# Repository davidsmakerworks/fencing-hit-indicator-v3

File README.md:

# fencing-hit-indicator-v3
 Fencing hit indicator with score display

## Possible future enhancements:
* Add score increment pads on PCB
* Redesign PCB for more efficient space usage
* Design separate LED PCBs with ribbon cable from main PCB
* Add bout clock
* Add compile-time option to select PWM buzzer or active buzzer
* Reduce LED current (increase value of R2 and R3)

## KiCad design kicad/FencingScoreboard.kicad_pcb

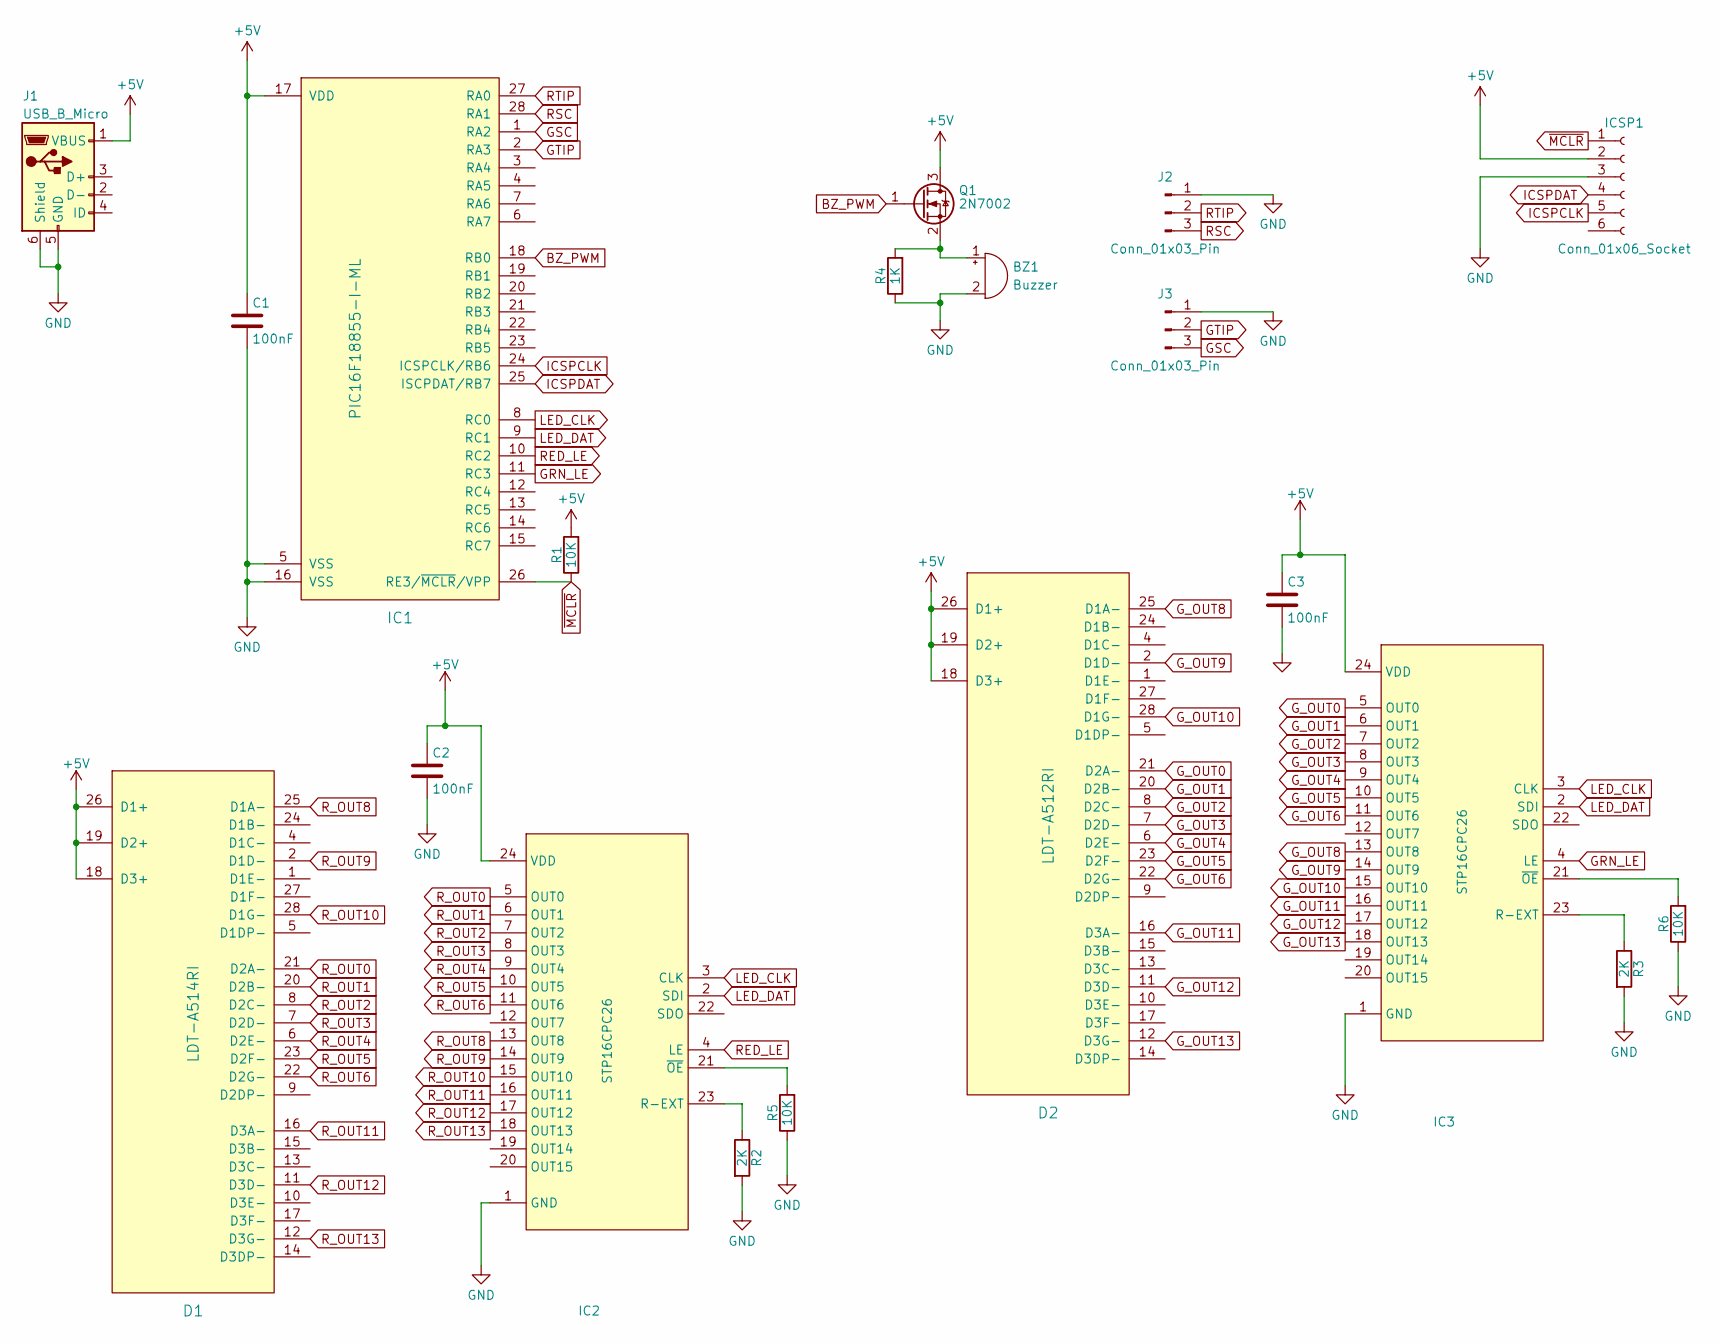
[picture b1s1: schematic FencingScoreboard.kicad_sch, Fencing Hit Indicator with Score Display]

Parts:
BZ1: Buzzer; MagneticBuzzer_ProSignal_ABT-410-RC
C1, C2, C3: 100nF; C_0603_1608Metric
D1: LDT-A514RI; LDT-x51xRI
D2: LDT-A512RI; LDT-x51xRI
IC1: PIC16F18855-I-ML; QFN-28-1EP_6x6mm_P0.65mm_EP4.25x4.25mm
IC2, IC3: STP16CPC26; SOP-24_7.5x15.4mm_P1.27mm
ICSP1: Conn_01x06_Socket; PinHeader_1x06_P2.54mm_Vertical
J1: USB_B_Micro; Molex_105164-0001_MicroUSB
J2, J3: Conn_01x03_Pin; PinHeader_1x03_P2.54mm_Vertical
Q1: 2N7002; SOT-23
R1, R5, R6: 10K; R_0805_2012Metric
R2, R3: 2K; R_0805_2012Metric
R4: 1K; R_0805_2012Metric

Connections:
+5V: C1.1, C2.1, C3.1, D1.18 (D3+), D1.19 (D2+), D1.26 (D1+), D2.18 (D3+), D2.19 (D2+), D2.26 (D1+), IC1.17 (VDD), IC2.24 (VDD), IC3.24 (VDD), ICSP1.2, J1.1 (VBUS), Q1.3 (D), R1.2
BZ_PWM: IC1.18 (RB0), Q1.1 (G)
GND: BZ1.2 (+), C1.2, C2.2, C3.2, IC1.5 (VSS), IC1.16 (VSS), IC2.1 (GND), IC3.1 (GND), ICSP1.3, J1.5 (GND), J1.6 (Shield), J2.1, J3.1, R2.2, R3.2, R4.1, R5.1, R6.1
GRN_LE: IC1.11 (RC3), IC3.4 (LE)
GSC: IC1.1 (RA2), J3.3
GTIP: IC1.2 (RA3), J3.2
G_OUT0: D2.21 (D2A-), IC3.5 (OUT0)
G_OUT1: D2.20 (D2B-), IC3.6 (OUT1)
G_OUT2: D2.8 (D2C-), IC3.7 (OUT2)
G_OUT3: D2.7 (D2D-), IC3.8 (OUT3)
G_OUT4: D2.6 (D2E-), IC3.9 (OUT4)
G_OUT5: D2.23 (D2F-), IC3.10 (OUT5)
G_OUT6: D2.22 (D2G-), IC3.11 (OUT6)
G_OUT8: D2.25 (D1A-), IC3.13 (OUT8)
G_OUT9: D2.2 (D1D-), IC3.14 (OUT9)
G_OUT10: D2.28 (D1G-), IC3.15 (OUT10)
G_OUT11: D2.16 (D3A-), IC3.16 (OUT11)
G_OUT12: D2.11 (D3D-), IC3.17 (OUT12)
G_OUT13: D2.12 (D3G-), IC3.18 (OUT13)
ICSPCLK: IC1.24 (ICSPCLK/RB6), ICSP1.5
ICSPDAT: IC1.25 (ISCPDAT/RB7), ICSP1.4
LED_CLK: IC1.8 (RC0), IC2.3 (CLK), IC3.3 (CLK)
LED_DAT: IC1.9 (RC1), IC2.2 (SDI), IC3.2 (SDI)
unnamed: BZ1.1 (-), Q1.2 (S), R4.2
unnamed: IC2.23 (R-EXT), R2.1
unnamed: IC2.21 (~OE), R5.2
unnamed: IC3.23 (R-EXT), R3.1
unnamed: IC3.21 (~OE), R6.2
RED_LE: IC1.10 (RC2), IC2.4 (LE)
RSC: IC1.28 (RA1), J2.3
RTIP: IC1.27 (RA0), J2.2
R_OUT0: D1.21 (D2A-), IC2.5 (OUT0)
R_OUT1: D1.20 (D2B-), IC2.6 (OUT1)
R_OUT2: D1.8 (D2C-), IC2.7 (OUT2)
R_OUT3: D1.7 (D2D-), IC2.8 (OUT3)
R_OUT4: D1.6 (D2E-), IC2.9 (OUT4)
R_OUT5: D1.23 (D2F-), IC2.10 (OUT5)
R_OUT6: D1.22 (D2G-), IC2.11 (OUT6)
R_OUT8: D1.25 (D1A-), IC2.13 (OUT8)
R_OUT9: D1.2 (D1D-), IC2.14 (OUT9)
R_OUT10: D1.28 (D1G-), IC2.15 (OUT10)
R_OUT11: D1.16 (D3A-), IC2.16 (OUT11)
R_OUT12: D1.11 (D3D-), IC2.17 (OUT12)
R_OUT13: D1.12 (D3G-), IC2.18 (OUT13)
~MCLR: IC1.26 (RE3/~MCLR/VPP), ICSP1.1, R1.1

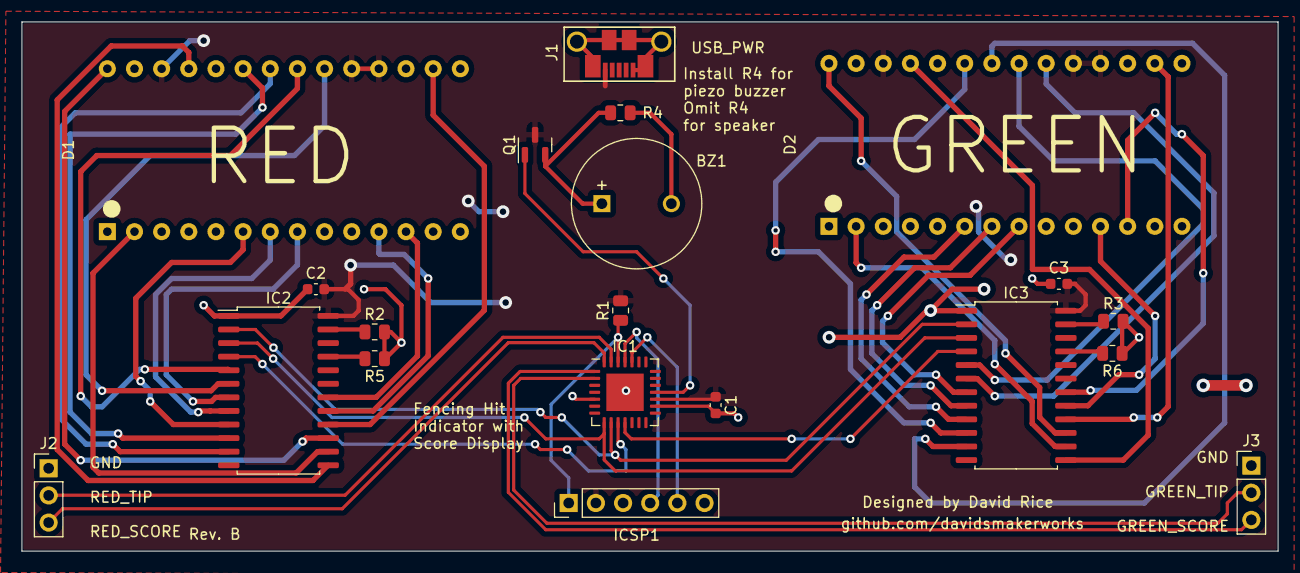
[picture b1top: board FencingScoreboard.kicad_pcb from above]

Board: 2 copper layers, 117.5 x 49.5 mm, 20 parts (0 on the bottom side), 45 nets.

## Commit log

2023-06-28 Minimal working version
2023-07-01 Add score limit and auto-reset
2023-07-01 Comments and minor cleanup
2023-07-05 Change score cooldown handling
2023-08-22 Add debugging LEDs for troubleshooting
2023-08-29 Fix timer atomicity bug, update device pack
2023-08-30 Fix timer atomicity bug
2023-10-23 Add KiCad project
2023-10-30 Schematic design
2023-10-31 PCB development
2024-01-02 Redesign for new LED driver, route PCB
2024-01-03 Update design rules, remove thermal vias
2024-01-03 Minor updates
2024-01-03 Update design rules
2024-01-08 Correct for PPS port restrictions, schematic cleanup
2024-01-09 Schematic cleanup, start PCB re-route
2024-01-13 PWM development
2024-01-18 Re-route PCB, update toolchain and device pack
2024-01-20 Implement new LED driver code and active buzzer, other minor updates
2024-01-22 Update for PWM buzzer
2024-01-25 Update J2, J3, BZ1 footprints
2024-02-04 Correct LE handling and port assignments
2024-03-01 Upgrade to KiCad 8.0 format
2025-01-05 Show which fencer hit first on LED display
2025-05-12 Update timer prescaler and pitches for buzzer
